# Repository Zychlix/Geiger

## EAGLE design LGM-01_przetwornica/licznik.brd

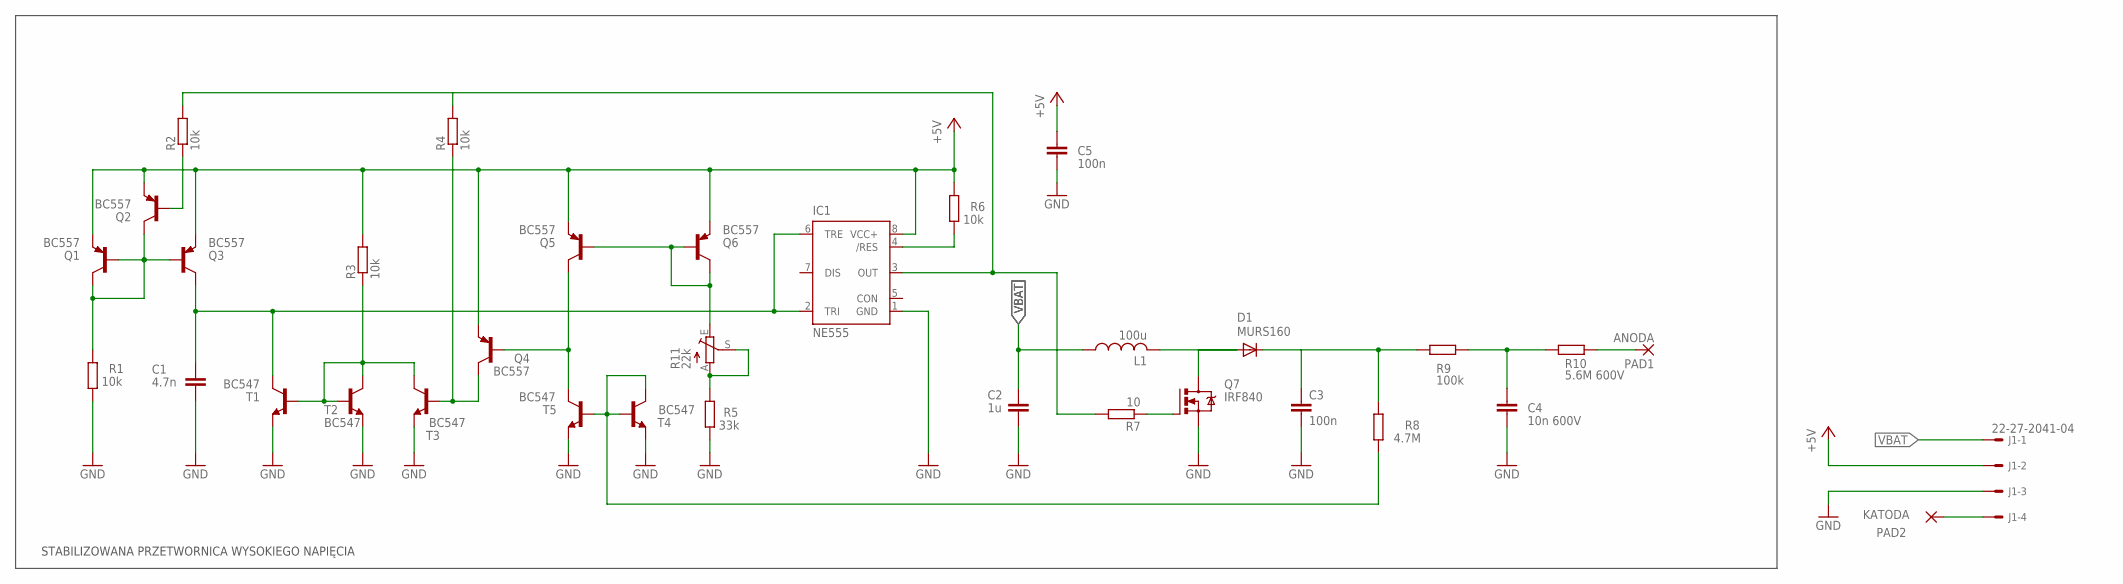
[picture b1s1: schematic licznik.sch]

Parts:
C1: 4.7n; C5B3
C2: 1u; C5B3
C3: 100n; C075-032X103
C4: 10n 600V; C5B3
C5: 100n; C5B3
D1: MURS160; SMB
IC1: NE555; DIL-08
J1: 22-27-2041-04; 6410-04
L1: 100u; TJ3-U1
PAD1: ANODA; 2,15/1,0
PAD2: KATODA; 2,15/1,0
Q1, Q2, Q3, Q4, Q5, Q6: BC557; TO92
Q7: IRF840; TO220BV
R1, R2, R3, R4, R6: 10k; 0207/10
R5: 33k; 0207/10
R7: 10; 0207/10
R8: 4.7M; 0207/10
R9: 100k; 0207/10
R10: 5.6M 600V; 0411/12
R11: 22k; CA6V
T1, T2, T3, T4, T5: BC547; TO92

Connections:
+5V: C5.1, IC1.8 (VCC+), J1.2, Q1.1 (E), Q2.1 (E), Q3.1 (E), Q4.1 (E), Q5.1 (E), Q6.1 (E), R3.2, R6.2
GND: C1.2, C2.2, C3.2, C4.2, C5.2, IC1.1 (GND), J1.3, Q7.S, R1.1, R5.1, T1.1 (E), T2.1 (E), T3.1 (E), T4.1 (E), T5.1 (E)
unnamed: C3.1, D1.C, R8.2, R9.2
unnamed: Q4.3 (C), R4.1, T3.2 (B)
unnamed: IC1.3 (OUT), R2.2, R4.2, R7.2
unnamed: Q1.2 (B), Q1.3 (C), Q2.3 (C), Q3.2 (B), R1.2
unnamed: C1.1, IC1.2 (TRI), IC1.6 (TRE), Q3.3 (C), T1.3 (C)
unnamed: D1.A, L1.2, Q7.D
unnamed: R3.1, T1.2 (B), T2.2 (B), T2.3 (C), T3.3 (C)
unnamed: Q2.2 (B), R2.1
unnamed: Q7.G, R7.1
unnamed: C4.1, R9.1, R10.1
unnamed: Q5.2 (B), Q6.2 (B), Q6.3 (C), R11.E
unnamed: R8.1, T4.2 (B), T5.2 (B), T5.3 (C)
unnamed: Q4.2 (B), Q5.3 (C), T4.3 (C)
unnamed: R5.2, R11.A, R11.S
unnamed: IC1.4 (/RES), R6.1
unnamed: PAD1.1, R10.2
unnamed: J1.4, PAD2.1
VBAT: C2.1, J1.1, L1.1

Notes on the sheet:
STABILIZOWANA PRZETWORNICA WYSOKIEGO NAPIĘCIA

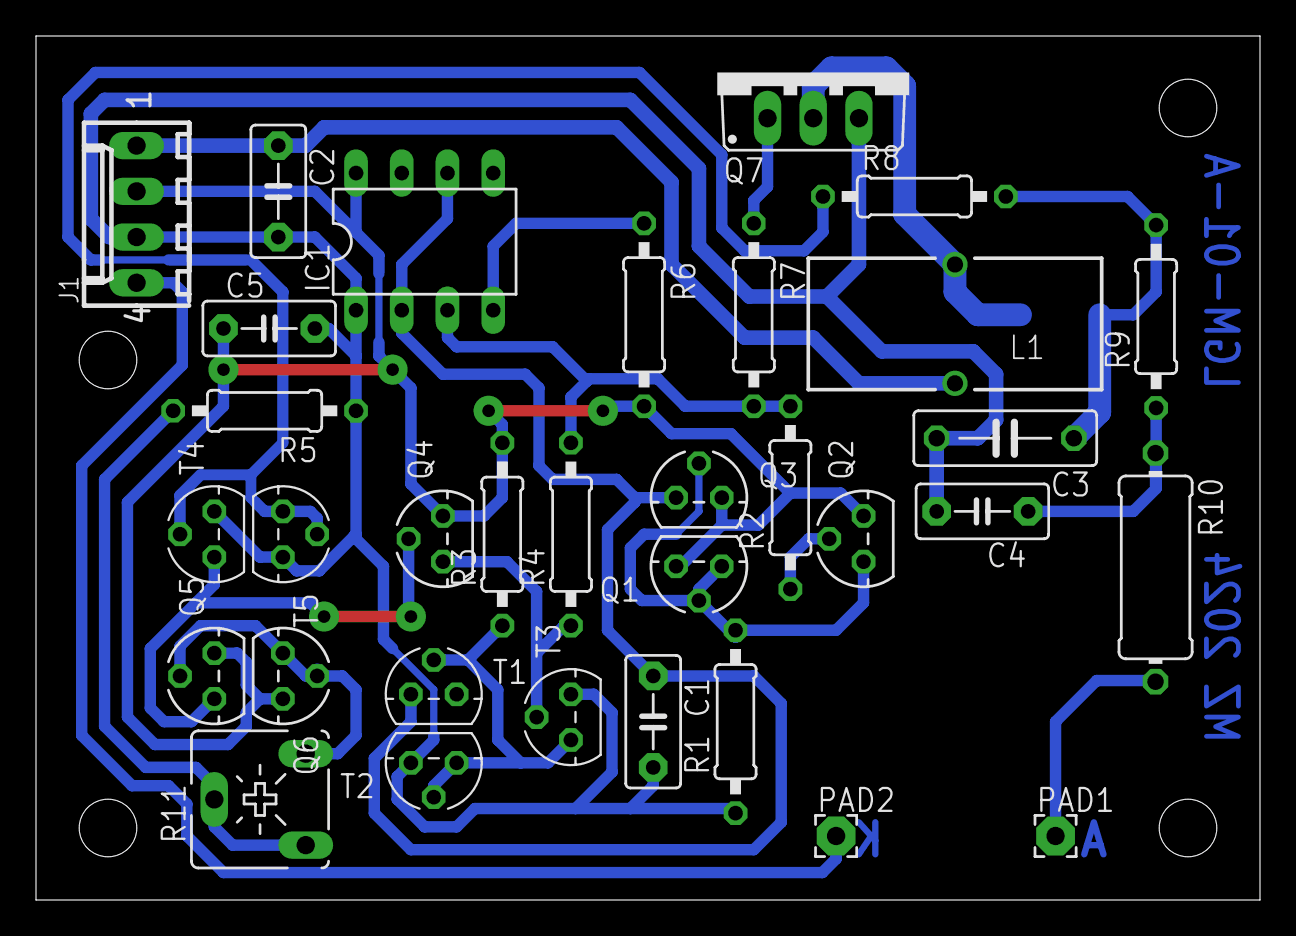
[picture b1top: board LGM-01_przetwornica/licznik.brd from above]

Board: 2 copper layers, 68.0 x 48.0 mm, 34 parts (1 on the bottom side), 20 nets.

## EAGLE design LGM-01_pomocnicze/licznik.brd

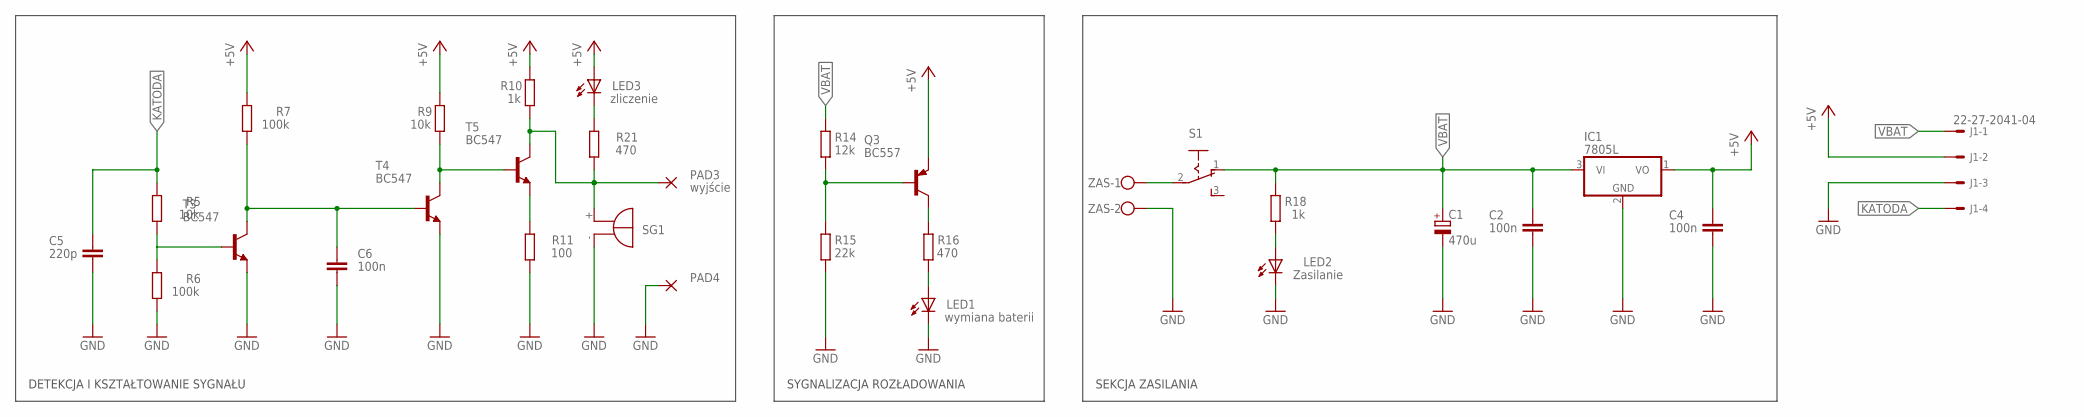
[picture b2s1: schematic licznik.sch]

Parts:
C1: 470u; E3,5-8
C2, C4, C6: 100n; C5B3
C5: 220p; C5B3
IC1: 7805L; TO92
J1: 22-27-2041-04; 6410-04
LED1: wymiana baterii; LED3MM
LED2: Zasilanie; LED3MM
LED3: zliczenie; LED3MM
PAD3: wyjście; 2,15/1,0
PAD4: WIREPAD2,15/1,0; 2,15/1,0
Q3: BC557; TO92
R5, R9: 10k; 0207/10
R6, R7: 100k; 0207/10
R10, R18: 1k; 0207/10
R11: 100; 0207/10
R14: 12k; 0207/10
R15: 22k; 0207/10
R16, R21: 470; 0207/10
S1: 255SB
SG1: F/QMBIII
T3, T4, T5: BC547; TO92
ZAS: W237-102

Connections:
+5V: C4.1, IC1.1 (VO), J1.2, LED3.A, Q3.1 (E), R7.2, R9.2, R10.2
GND: C1.-, C2.2, C4.2, C5.2, C6.2, IC1.2 (GND), J1.3, LED1.K (C), LED2.K (C), PAD4.1, R6.1, R11.1, R15.1, SG1.- (+), T3.1 (E), T4.1 (E), ZAS.2
KATODA: C5.1, J1.4, R5.2
unnamed: LED2.A, R18.1
unnamed: LED1.A, R16.1
unnamed: R5.1, R6.2, T3.2 (B)
unnamed: C6.1, R7.1, T3.3 (C), T4.2 (B)
unnamed: R11.2, T5.1 (E)
unnamed: S1.2, ZAS.1
unnamed: R9.1, T4.3 (C), T5.2 (B)
unnamed: Q3.3 (C), R16.2
unnamed: Q3.2 (B), R14.1, R15.2
unnamed: LED3.K (C), R21.2
VBAT: C1.+, C2.1, IC1.3 (VI), J1.1, R14.2, R18.2, S1.1 (O)
WYJSCIE: PAD3.1, R10.1, R21.1, SG1.+ (-), T5.3 (C)

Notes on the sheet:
DETEKCJA I KSZTAŁTOWANIE SYGNAŁU
SYGNALIZACJA ROZŁADOWANIA
SEKCJA ZASILANIA

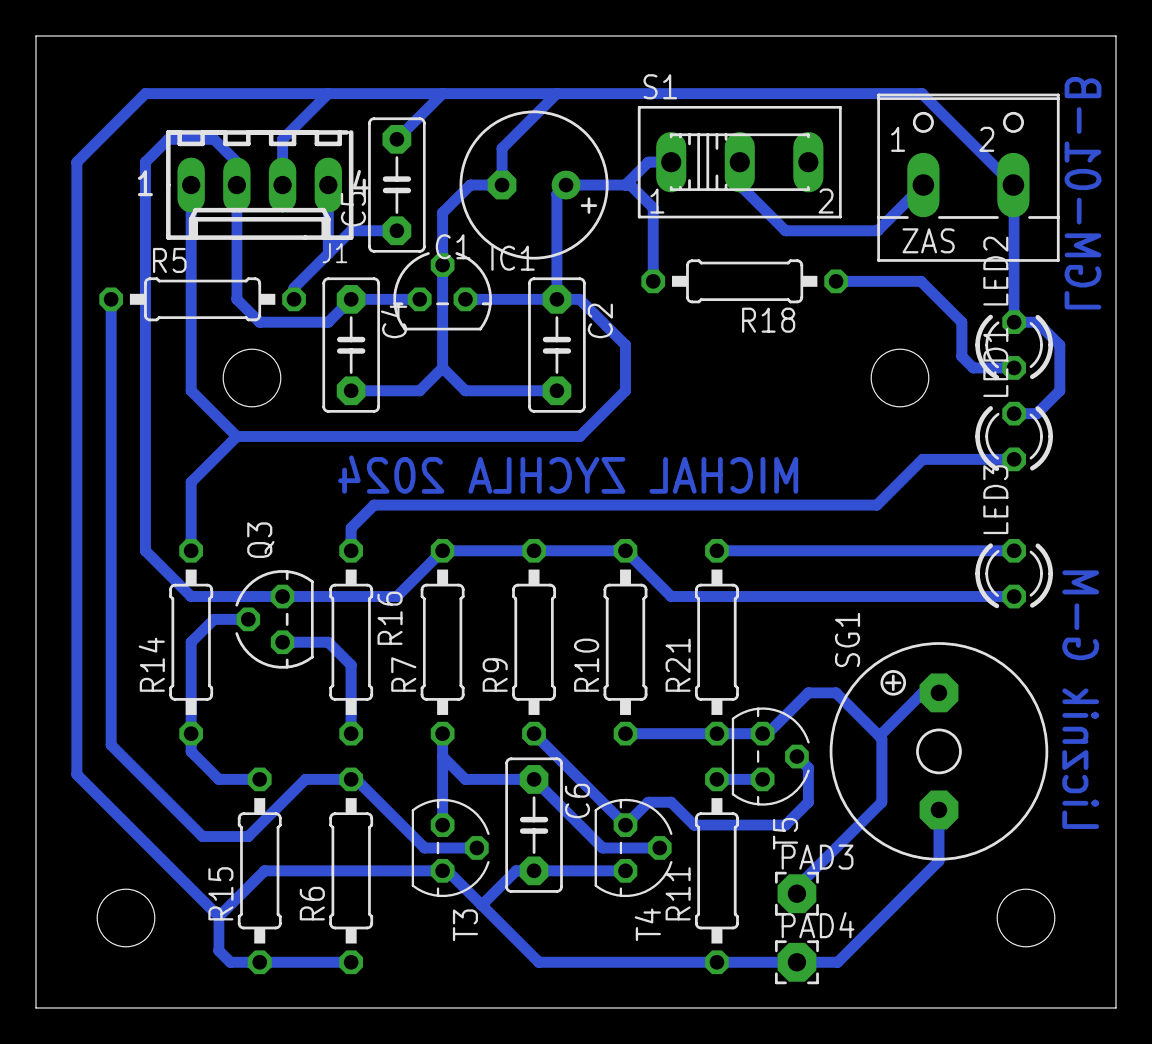
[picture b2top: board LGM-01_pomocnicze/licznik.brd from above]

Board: 2 copper layers, 60.0 x 54.0 mm, 30 parts (0 on the bottom side), 15 nets.

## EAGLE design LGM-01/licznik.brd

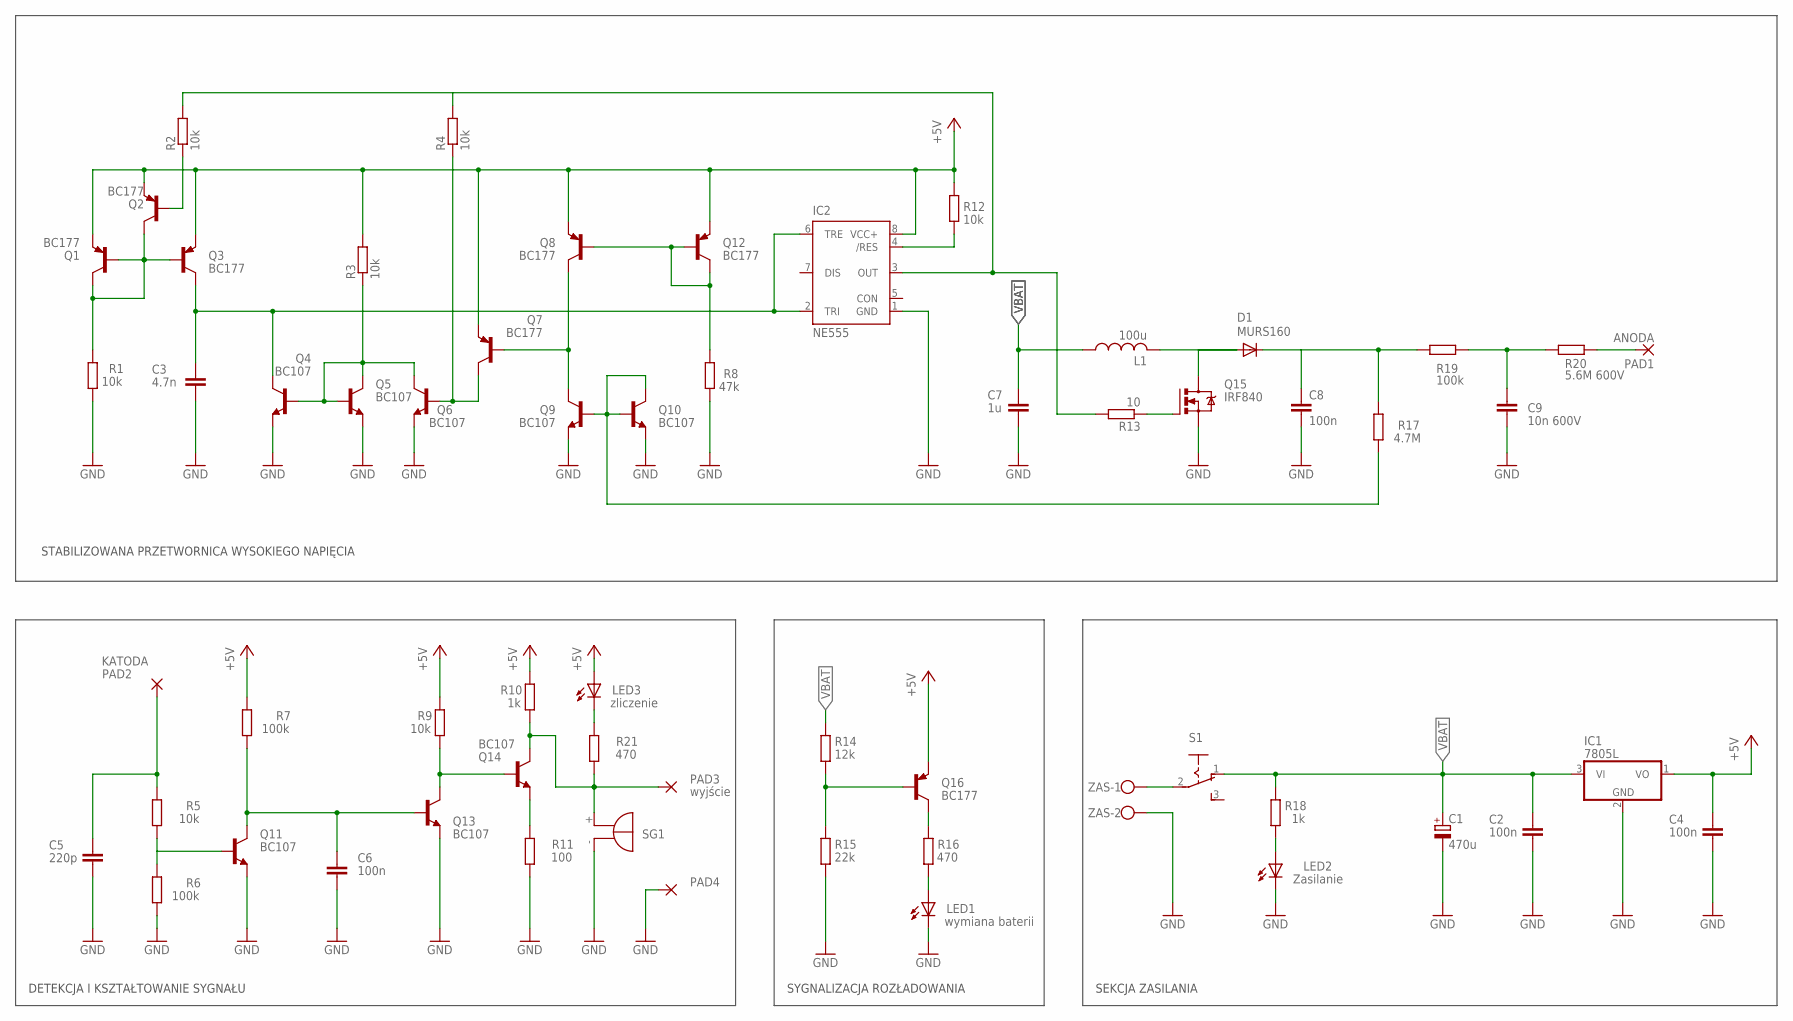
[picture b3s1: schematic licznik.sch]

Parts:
C1: 470u; E3,5-8
C2, C4, C6: 100n; C5B3
C3: 4.7n; C5B3
C5: 220p; C5B3
C7: 1u; C5B3
C8: 100n; C075-032X103
C9: 10n 600V; C5B3
D1: MURS160; SMB
IC1: 7805L; TO92
IC2: NE555; DIL-08
L1: 100u; TJ3-U1
LED1: wymiana baterii; LED3MM
LED2: Zasilanie; LED3MM
LED3: zliczenie; LED3MM
PAD1: ANODA; 2,15/1,0
PAD2: KATODA; 2,15/1,0
PAD3: wyjście; 2,15/1,0
PAD4: WIREPAD2,15/1,0; 2,15/1,0
Q1, Q2, Q3, Q7, Q8, Q12, Q16: BC177; TO18
Q4, Q5, Q6, Q9, Q10, Q11, Q13, Q14: BC107; TO18
Q15: IRF840; TO220BV
R1, R2, R3, R4, R5, R9, R12: 10k; 0207/10
R6, R7, R19: 100k; 0207/10
R8: 47k; 0207/10
R10, R18: 1k; 0207/10
R11: 100; 0207/10
R13: 10; 0207/10
R14: 12k; 0207/10
R15: 22k; 0207/10
R16, R21: 470; 0207/10
R17: 4.7M; 0207/10
R20: 5.6M 600V; 0411/12
S1: 255SB
SG1: F/QMBIII
ZAS: W237-102

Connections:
+5V: C4.1, IC1.1 (VO), IC2.8 (VCC+), LED3.A, Q1.1 (E), Q2.1 (E), Q3.1 (E), Q7.1 (E), Q8.1 (E), Q12.1 (E), Q16.1 (E), R3.2, R7.2, R9.2, R10.2, R12.2
GND: C1.-, C2.2, C3.2, C4.2, C5.2, C6.2, C7.2, C8.2, C9.2, IC1.2 (GND), IC2.1 (GND), LED1.K (C), LED2.K (C), PAD4.1, Q4.1 (E), Q5.1 (E), Q6.1 (E), Q9.1 (E), Q10.1 (E), Q11.1 (E), Q13.1 (E), Q15.S, R1.1, R6.1, R8.1, R11.1, R15.1, SG1.- (+), ZAS.2
KATODA: C5.1, PAD2.1, R5.2
unnamed: C8.1, D1.C, R17.2, R19.2
unnamed: Q6.2 (B), Q7.3 (C), R4.1
unnamed: IC2.3 (OUT), R2.2, R4.2, R13.2
unnamed: Q1.2 (B), Q1.3 (C), Q2.3 (C), Q3.2 (B), R1.2
unnamed: C3.1, IC2.2 (TRI), IC2.6 (TRE), Q3.3 (C), Q4.3 (C)
unnamed: D1.A, L1.2, Q15.D
unnamed: Q4.2 (B), Q5.2 (B), Q5.3 (C), Q6.3 (C), R3.1
unnamed: Q2.2 (B), R2.1
unnamed: Q15.G, R13.1
unnamed: C9.1, R19.1, R20.1
unnamed: Q8.2 (B), Q12.2 (B), Q12.3 (C), R8.2
unnamed: Q9.2 (B), Q10.2 (B), Q10.3 (C), R17.1
unnamed: Q7.2 (B), Q8.3 (C), Q9.3 (C)
unnamed: LED2.A, R18.1
unnamed: LED1.A, R16.1
unnamed: IC2.4 (/RES), R12.1
unnamed: Q11.2 (B), R5.1, R6.2
unnamed: C6.1, Q11.3 (C), Q13.2 (B), R7.1
unnamed: Q14.1 (E), R11.2
unnamed: S1.2, ZAS.1
unnamed: Q13.3 (C), Q14.2 (B), R9.1
unnamed: Q16.3 (C), R16.2
unnamed: Q16.2 (B), R14.1, R15.2
unnamed: LED3.K (C), R21.2
unnamed: PAD1.1, R20.2
VBAT: C1.+, C2.1, C7.1, IC1.3 (VI), L1.1, R14.2, R18.2, S1.1 (O)
WYJSCIE: PAD3.1, Q14.3 (C), R10.1, R21.1, SG1.+ (-)

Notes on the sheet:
STABILIZOWANA PRZETWORNICA WYSOKIEGO NAPIĘCIA
DETEKCJA I KSZTAŁTOWANIE SYGNAŁU
SYGNALIZACJA ROZŁADOWANIA
SEKCJA ZASILANIA

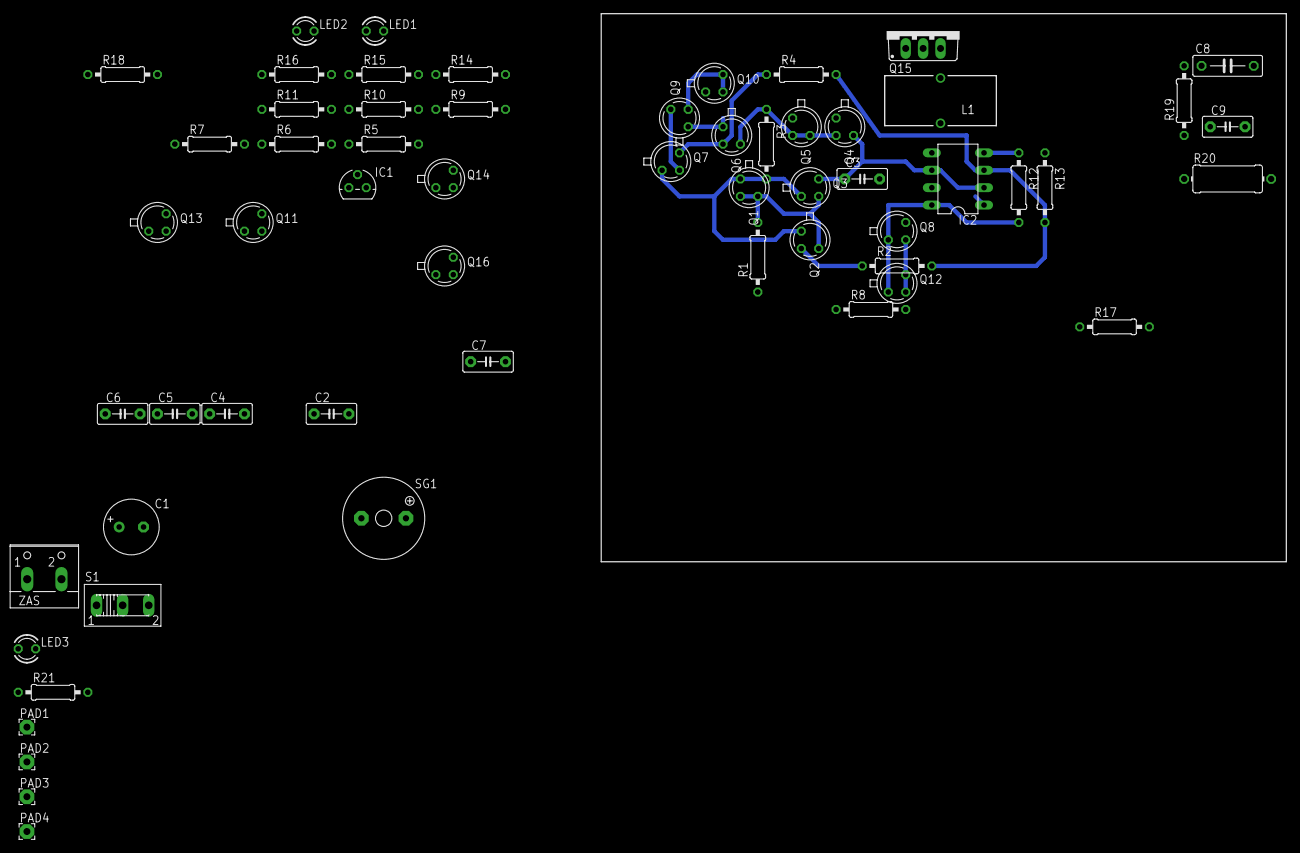
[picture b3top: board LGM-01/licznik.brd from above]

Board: 2 copper layers, 100.0 x 80.0 mm, 60 parts (1 on the bottom side), 30 nets.

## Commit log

2024-03-24 Wstepny
2024-03-24 edycje
2024-04-21 Geiger SMPS made
2024-04-21 Geiger SMPS cleanup
2024-04-21 Added auxilary board
2024-04-22 Boards complete
2024-06-09 Backup
